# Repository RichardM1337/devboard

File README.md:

# Devboard
This is my first devboard. It's my introduction to more advanced concepts

This was probably one of the hardest projects I have done ever. The wiring made me want to cry but we were able to get through it. Looking back, I think I've came very far and I'm really happy about my progress.

# PCB
The devboard PCB was made entirely on KiCAD

- Schematic
- 
- PCB Design
- 

# 3D Model
This 3d model of the devboard was made within the 3d viewer in KiCAD

- Front
- 
- Back
- 

# BOM Bill of Materials

| Quantity | Comment                     | Designator          | Footprint                                   | Link                                               |
|----------|-----------------------------|---------------------|---------------------------------------------|----------------------------------------------------|
| 11       | 0.1uF                       | C2-9, C11, C12, C17 | C_0402_1005Metric                           | https://www.lcsc.com/product-detail/C1525.html     |
| 2        | 5.1K                        | R1, R2              | R_0402_1005Metric                           | https://www.lcsc.com/product-detail/C25905.html    |
| 1        | SW_Push                     | SW1, SW2            | SW_Push_SPST_NO_Alps_SKRK                   | https://www.lcsc.com/product-detail/C720477.html   |
| 2        | 10uF                        | C13, C14            | C_0603_1608Metric                           | https://www.lcsc.com/product-detail/C19702.html    |
| 2        | 33pF                        | C15, C16            | C_0402_1005Metric                           | https://www.lcsc.com/product-detail/C107047.html   |
| 2        | 1K                          | R5, R7              | R_0402_1005Metric                           | https://www.lcsc.com/product-detail/C11702.html    |
| 2        | 10K                         | R6, R8              | R_0402_1005Metric                           | https://www.lcsc.com/product-detail/C60490.html    |
| 1        | W25Q128JVS                  | U3                  | Winbond_USON-8-1EP_3x2mm_P0.5mm_EP0.2x1.6mm | https://www.lcsc.com/product-detail/C2456208.html  |
| 2        | Conn_01x20                  | J2, J3              | PinHeader_1x20_P2.54mm_Vertical             | https://www.lcsc.com/product-detail/C42431804.html |
| 1        | Conn_01x03                  | J4                  | PinHeader_1x03_P2.54mm_Vertical             | https://www.lcsc.com/product-detail/C32713269.html |
| 1        | MCP1700x-330xxTT            | U4                  | SOT-23                                      | https://www.lcsc.com/product-detail/C39051.html    |
| 1        | 12MHz                       | Y1                  | Crystal_SMD_3225-4Pin_3.2x2.5mm             | https://www.lcsc.com/product-detail/C9002.html     |
| 2        | 27                          | R3, R4              | R_0402_1005Metric                           | https://www.lcsc.com/product-detail/C25100.html    |
| 2        | 1uF                         | C1, C10             | C_0402_1005Metric                           | https://www.lcsc.com/product-detail/C29266.html    |
| 1        | USB_C_Receptacle_USB2.0_14P | J1                  | USB_C_Receptacle_HRO_TYPE-C-31-M-12         | https://www.lcsc.com/product-detail/C165948.html   |
| 1        | RP2040                      | U1                  | QFN-56-1EP_7x7mm_P0.4mm_EP3.2x3.2mm         | https://www.lcsc.com/product-detail/C2040.html     |
| PCBA Estimated Price| $50.84

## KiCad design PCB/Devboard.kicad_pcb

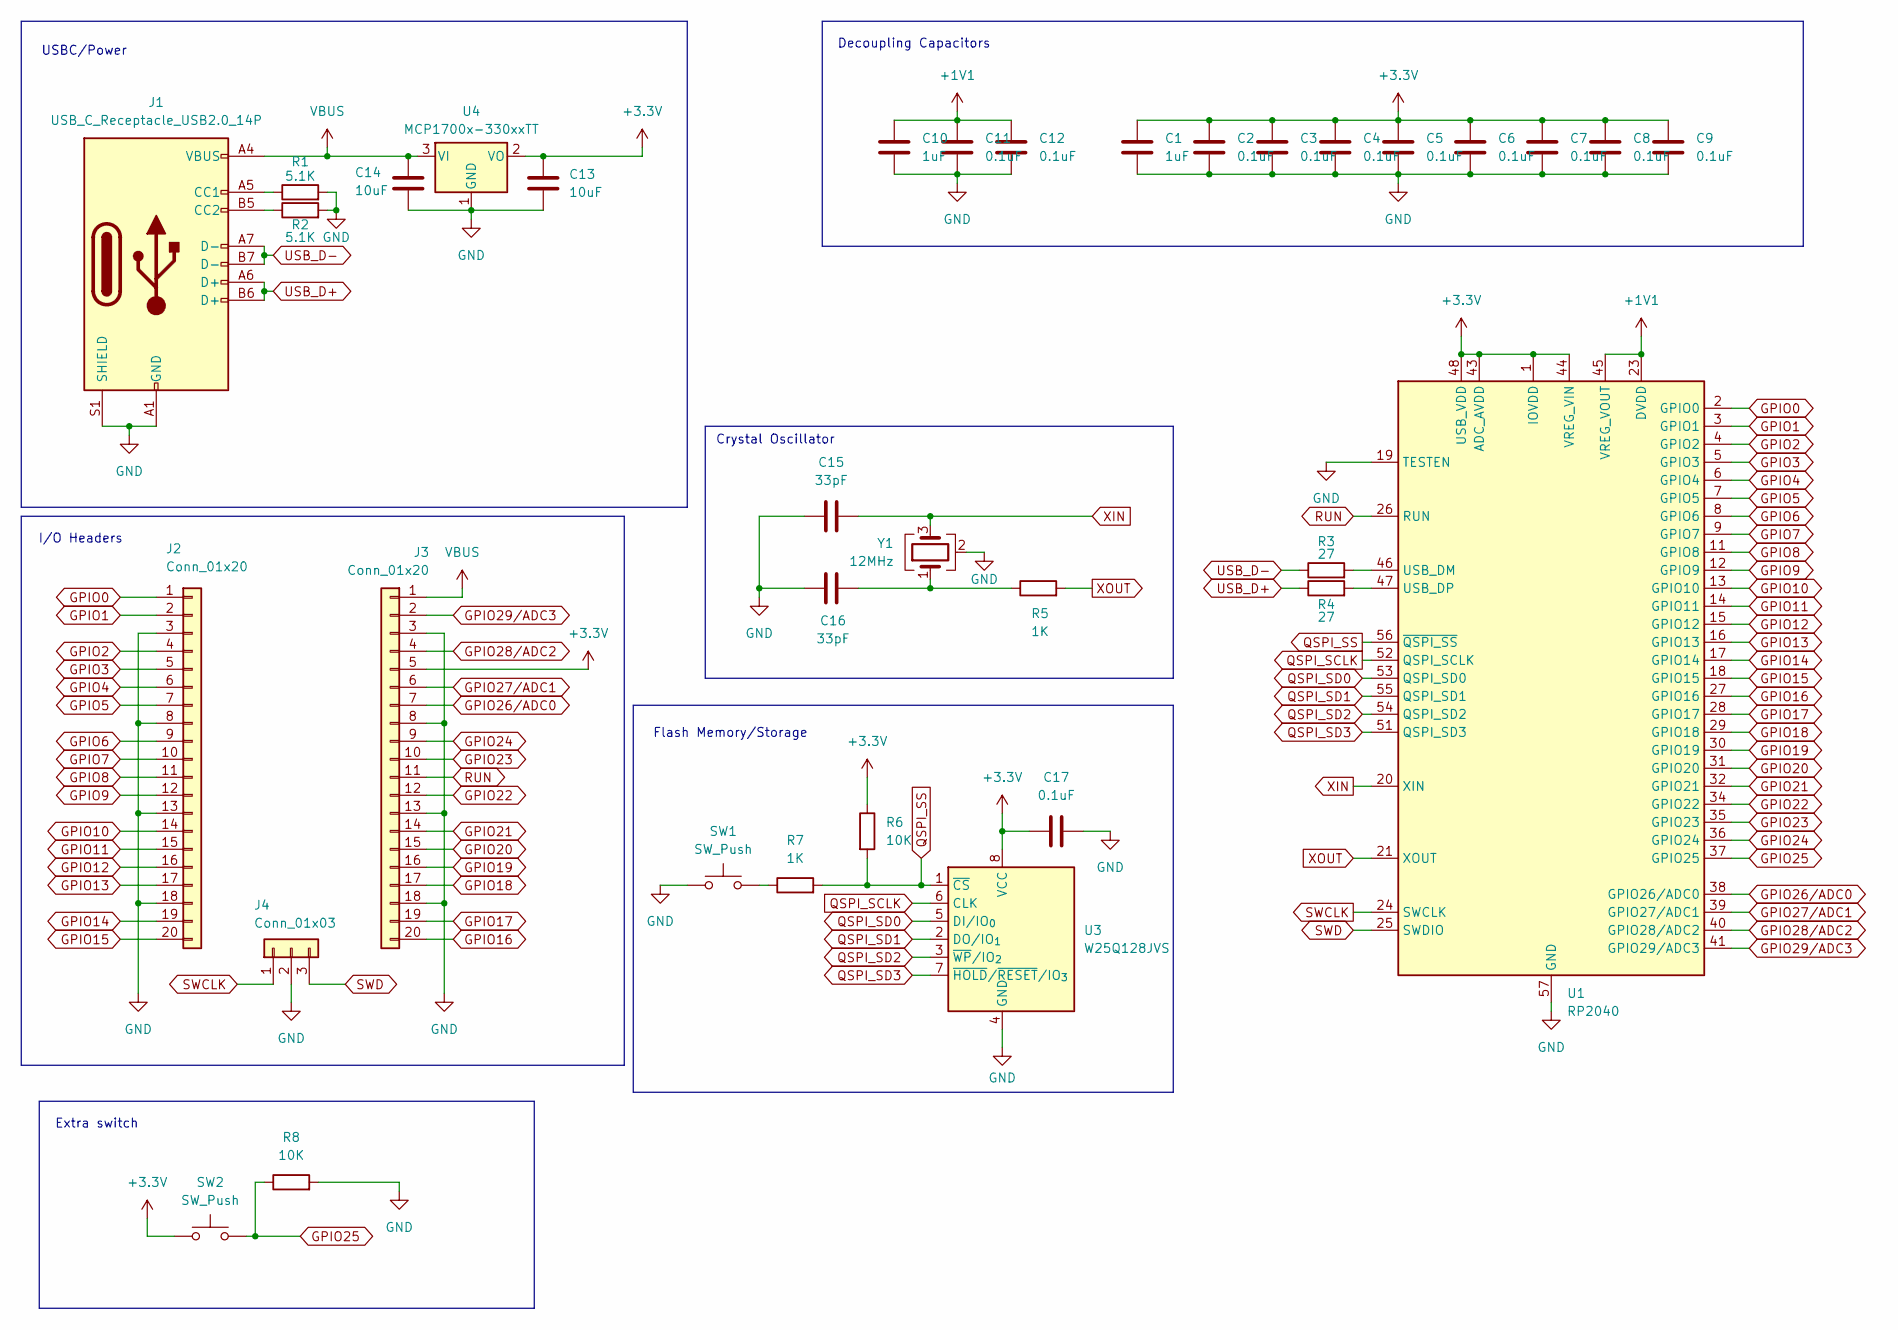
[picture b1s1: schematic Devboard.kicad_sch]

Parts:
C1, C10: 1uF; C_0402_1005Metric
C2, C3, C4, C5, C6, C7, C8, C9, C11, C12, C17: 0.1uF; C_0402_1005Metric
C13, C14: 10uF; C_0603_1608Metric
C15, C16: 33pF; C_0402_1005Metric
J1: USB_C_Receptacle_USB2.0_14P; USB_C_Receptacle_HRO_TYPE-C-31-M-12
J2, J3: Conn_01x20; PinHeader_1x20_P2.54mm_Vertical
J4: Conn_01x03; PinHeader_1x03_P2.54mm_Vertical
R1, R2: 5.1K; R_0402_1005Metric
R3, R4: 27; R_0402_1005Metric
R5, R7: 1K; R_0402_1005Metric
R6, R8: 10K; R_0402_1005Metric
SW1, SW2: SW_Push; SW_Push_SPST_NO_Alps_SKRK
U1: RP2040; QFN-56-1EP_7x7mm_P0.4mm_EP3.2x3.2mm
U3: W25Q128JVS; Winbond_USON-8-1EP_3x2mm_P0.5mm_EP0.2x1.6mm
U4: MCP1700x-330xxTT; SOT-23
Y1: 12MHz; Crystal_SMD_3225-4Pin_3.2x2.5mm

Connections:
+1V1: C10.1, C11.1, C12.1, U1.23 (DVDD), U1.45 (VREG_VOUT), U1.50 (DVDD)
+3.3V: C1.1, C2.1, C3.1, C4.1, C5.1, C6.1, C7.1, C8.1, C9.1, C13.1, C17.1, J3.5, R6.1, SW2.1, U1.1 (IOVDD), U1.10 (IOVDD), U1.22 (IOVDD), U1.33 (IOVDD), U1.42 (IOVDD), U1.43 (ADC_AVDD), U1.44 (VREG_VIN), U1.48 (USB_VDD), U1.49 (IOVDD), U3.8 (VCC), U4.2 (VO)
GND: C1.2, C2.2, C3.2, C4.2, C5.2, C6.2, C7.2, C8.2, C9.2, C10.2, C11.2, C12.2, C13.2, C14.2, C15.1, C16.1, C17.2, J1.A1 (GND), J1.A12 (GND), J1.B1 (GND), J1.B12 (GND), J1.S1 (SHIELD), J2.3, J2.8, J2.13, J2.18, J3.3, J3.8, J3.13, J3.18, J4.2, R1.2, R2.2, R8.2, SW1.1, U1.19 (TESTEN), U1.57 (GND), U3.4 (GND), U4.1 (GND), Y1.2 (G), Y1.4 (G)
GPIO0: J2.1, U1.2 (GPIO0)
GPIO1: J2.2, U1.3 (GPIO1)
GPIO2: J2.4, U1.4 (GPIO2)
GPIO3: J2.5, U1.5 (GPIO3)
GPIO4: J2.6, U1.6 (GPIO4)
GPIO5: J2.7, U1.7 (GPIO5)
GPIO6: J2.9, U1.8 (GPIO6)
GPIO7: J2.10, U1.9 (GPIO7)
GPIO8: J2.11, U1.11 (GPIO8)
GPIO9: J2.12, U1.12 (GPIO9)
GPIO10: J2.14, U1.13 (GPIO10)
GPIO11: J2.15, U1.14 (GPIO11)
GPIO12: J2.16, U1.15 (GPIO12)
GPIO13: J2.17, U1.16 (GPIO13)
GPIO14: J2.19, U1.17 (GPIO14)
GPIO15: J2.20, U1.18 (GPIO15)
GPIO16: J3.20, U1.27 (GPIO16)
GPIO17: J3.19, U1.28 (GPIO17)
GPIO18: J3.17, U1.29 (GPIO18)
GPIO19: J3.16, U1.30 (GPIO19)
GPIO20: J3.15, U1.31 (GPIO20)
GPIO21: J3.14, U1.32 (GPIO21)
GPIO22: J3.12, U1.34 (GPIO22)
GPIO23: J3.10, U1.35 (GPIO23)
GPIO24: J3.9, U1.36 (GPIO24)
GPIO25: R8.1, SW2.2, U1.37 (GPIO25)
GPIO26/ADC0: J3.7, U1.38 (GPIO26/ADC0)
GPIO27/ADC1: J3.6, U1.39 (GPIO27/ADC1)
GPIO28/ADC2: J3.4, U1.40 (GPIO28/ADC2)
GPIO29/ADC3: J3.2, U1.41 (GPIO29/ADC3)
unnamed: C16.2, R5.1, Y1.1
unnamed: J1.A5 (CC1), R1.1
unnamed: J1.B5 (CC2), R2.1
unnamed: R7.1, SW1.2
unnamed: R3.2, U1.46 (USB_DM)
unnamed: R4.2, U1.47 (USB_DP)
QSPI_SCLK: U1.52 (QSPI_SCLK), U3.6 (CLK)
QSPI_SD0: U1.53 (QSPI_SD0), U3.5 (DI/IO_{0})
QSPI_SD1: U1.55 (QSPI_SD1), U3.2 (DO/IO_{1})
QSPI_SD2: U1.54 (QSPI_SD2), U3.3 (~WP/IO_{2})
QSPI_SD3: U1.51 (QSPI_SD3), U3.7 (~HOLD/~RESET/IO_{3})
QSPI_SS: R6.2, R7.2, U1.56 (~QSPI_SS), U3.1 (~CS)
RUN: J3.11, U1.26 (RUN)
SWCLK: J4.1, U1.24 (SWCLK)
SWD: J4.3, U1.25 (SWDIO)
USB_D+: J1.A6 (D+), J1.B6 (D+), R4.1
USB_D-: J1.A7 (D-), J1.B7 (D-), R3.1
VBUS: C14.1, J1.A4 (VBUS), J1.A9 (VBUS), J1.B4 (VBUS), J1.B9 (VBUS), J3.1, U4.3 (VI)
XIN: C15.2, U1.20 (XIN), Y1.3
XOUT: R5.2, U1.21 (XOUT)

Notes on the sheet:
Flash Memory/Storage
I/O Headers
USBC/Power
Crystal Oscillator
Extra switch
Decoupling Capacitors

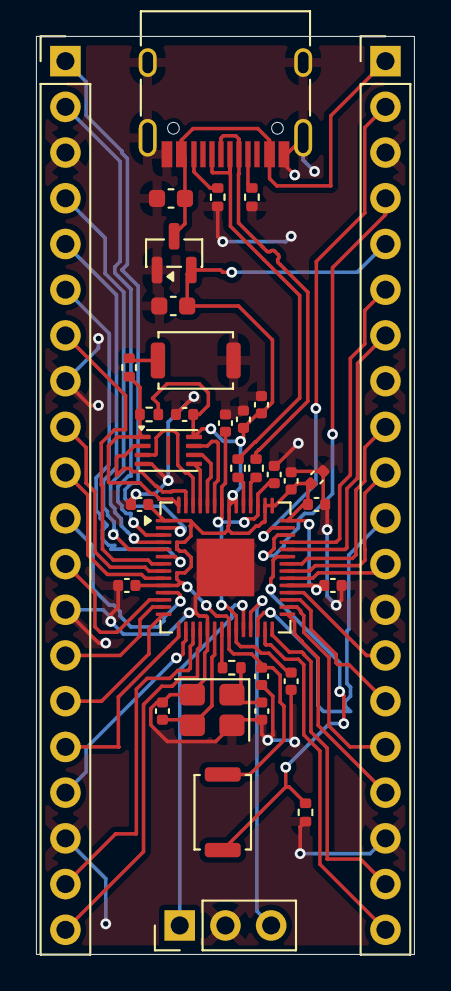
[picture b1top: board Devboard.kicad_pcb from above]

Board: 2 copper layers, 21.0 x 51.0 mm, 35 parts (0 on the bottom side), 53 nets.

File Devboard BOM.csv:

Quantity,Comment,Designator,Footprint,Link
11,0.1uF,"C2-9, C11, C12, C17",C_0402_1005Metric,https://www.lcsc.com/product-detail/C1525.html
2,5.1K,"R1, R2",R_0402_1005Metric,https://www.lcsc.com/product-detail/C25905.html
1,SW_Push,"SW1, SW2",SW_Push_SPST_NO_Alps_SKRK,https://www.lcsc.com/product-detail/C720477.html
2,10uF,"C13, C14",C_0603_1608Metric,https://www.lcsc.com/product-detail/C19702.html
2,33pF,"C15, C16",C_0402_1005Metric,https://www.lcsc.com/product-detail/C107047.html
2,1K,"R5, R7",R_0402_1005Metric,https://www.lcsc.com/product-detail/C11702.html
2,10K,"R6, R8",R_0402_1005Metric,https://www.lcsc.com/product-detail/C60490.html
1,W25Q128JVS,U3,Winbond_USON-8-1EP_3x2mm_P0.5mm_EP0.2x1.6mm,https://www.lcsc.com/product-detail/C2456208.html
2,Conn_01x20,"J2, J3",PinHeader_1x20_P2.54mm_Vertical,https://www.lcsc.com/product-detail/C42431804.html
1,Conn_01x03,J4,PinHeader_1x03_P2.54mm_Vertical,https://www.lcsc.com/product-detail/C32713269.html
1,MCP1700x-330xxTT,U4,SOT-23,https://www.lcsc.com/product-detail/C39051.html
1,12MHz,Y1,Crystal_SMD_3225-4Pin_3.2x2.5mm,https://www.lcsc.com/product-detail/C9002.html
2,27,"R3, R4",R_0402_1005Metric,https://www.lcsc.com/product-detail/C25100.html
2,1uF,"C1, C10",C_0402_1005Metric,https://www.lcsc.com/product-detail/C29266.html
1,USB_C_Receptacle_USB2.0_14P,J1,USB_C_Receptacle_HRO_TYPE-C-31-M-12,https://www.lcsc.com/product-detail/C165948.html
1,RP2040,U1,QFN-56-1EP_7x7mm_P0.4mm_EP3.2x3.2mm,https://www.lcsc.com/product-detail/C2040.html
PCBA Estimated Price,$50.84,,,

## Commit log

2026-05-04 Fix schematic image link in README
    Updated schematic image link to point to the main repository.
2026-05-04 Update image links in README.md to raw GitHub URLs
